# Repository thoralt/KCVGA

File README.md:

# KCVGA
This project aims to convert the video output of old KC85/4 computer systems into a VGA signal for display on a modern monitor. The hosts video signals are sampled from the mainboard into an SRAM using an Xilinx Spartan 3A FPGA. The FPGA also generates the VGA video signal from the sampled image. A PIC32MX250F128B contains the FPGA bitstream and loads it during power-up. Additionally, the PIC32 serves as a USB bridge to the FPGA.

## First Prototype

## Second Prototype

# Schematic

# FPGA

## Clock generation

The input clock of 48 MHz is being fed into a DCM to generate the video clock of 108 MHz. This clock drives the states of all other modules inside the FPGA (_KCVIDEO_INTERFACE_, _PIC32_INTERFACE_, _ROM_, _SRAM_INTERFACE_, _VGA_OUTPUT_ and the FIFOs).

## KCVIDEO_INTERFACE

The module _KCVIDEO_INTERFACE_ FPGA has the purpose to pull the pixel data off the mainboard while the KC85 is generating its video signal. It taps into the color and brightness signals (_R_, _G_, _B_, _EX_, _EZ_) as well as the clock signals (_KC_CLK_, _KC_HSYNC_, _KC_VSYNC_). 

To enhance the fault tolerance, the clock and synchronization signals are fed through glitch filters and edge detectors. A falling edge on _KC_VSYNC_ starts a new frame which resets the current line number and SRAM address. A falling edge on _KC_HSYNC_ resets the column counter. On every rising edge of the pixel clock _KC_CLK_ all five pixel data bits are read into a temporary register and the SRAM address ist incremented. After three pixels have been read, these pixels are combined with the 16 bit SRAM address to form a 31 bit wide data word which is being fed into a FIFO. This FIFO buffers 512 words and serves as a synchronization object between the _KCVIDEO_INTERFACE_ and the _SRAM_INTERFACE_.

## SRAM_INTERFACE

This module checks the FIFOs connected to _KCVIDEO_INTERFACE_ and _VGA_OUTPUT_ while preferring the _VGA_OUTPUT_ FIFO. The _VGA_OUTPUT_ module initiates a data transfer by writing a new address into the _SRAM_INTERFACE_. In return, the _SRAM_INTERFACE_ starts filling the FIFO with the content of one video line. If no VGA data transfer is active, the _SRAM_INTERFACE_ module checks the other FIFO for new pixel data, which is then written into the SRAM.

## VGA_OUTPUT

The _VGA_OUTPUT_ module generates the timing signals to create a valid VGA signal of 1280 by 1024 pixels. This mode was chosen because the pixels are integer divisible by the resolution of the KC85 (320 by 256). At the beginning of each line the module requests pixel data from the _SRAM_INTERFACE_ by writing a new address. The FIFO is then starting to fill and at the end of the horizontal sync pulse the first pixels are available to be written to the outputs. The KC pixel data is being mapped to a fixed color space of 4 bit R, G and B values.

## PIC32_INTERFACE

This module allows the PIC32 microcontroller to access the SRAM. Since the PIC32MX250F128B does not support USB High Speed, we're limited to approximately 1 megabyte per second which is close, but not enough to transport the 1.28 MB/s image stream (5 bits, 320 columns, 256 rows, 25 frames). An experimental video streaming implementation might be available later in the design process.

# PIC32 Firmware

tbd

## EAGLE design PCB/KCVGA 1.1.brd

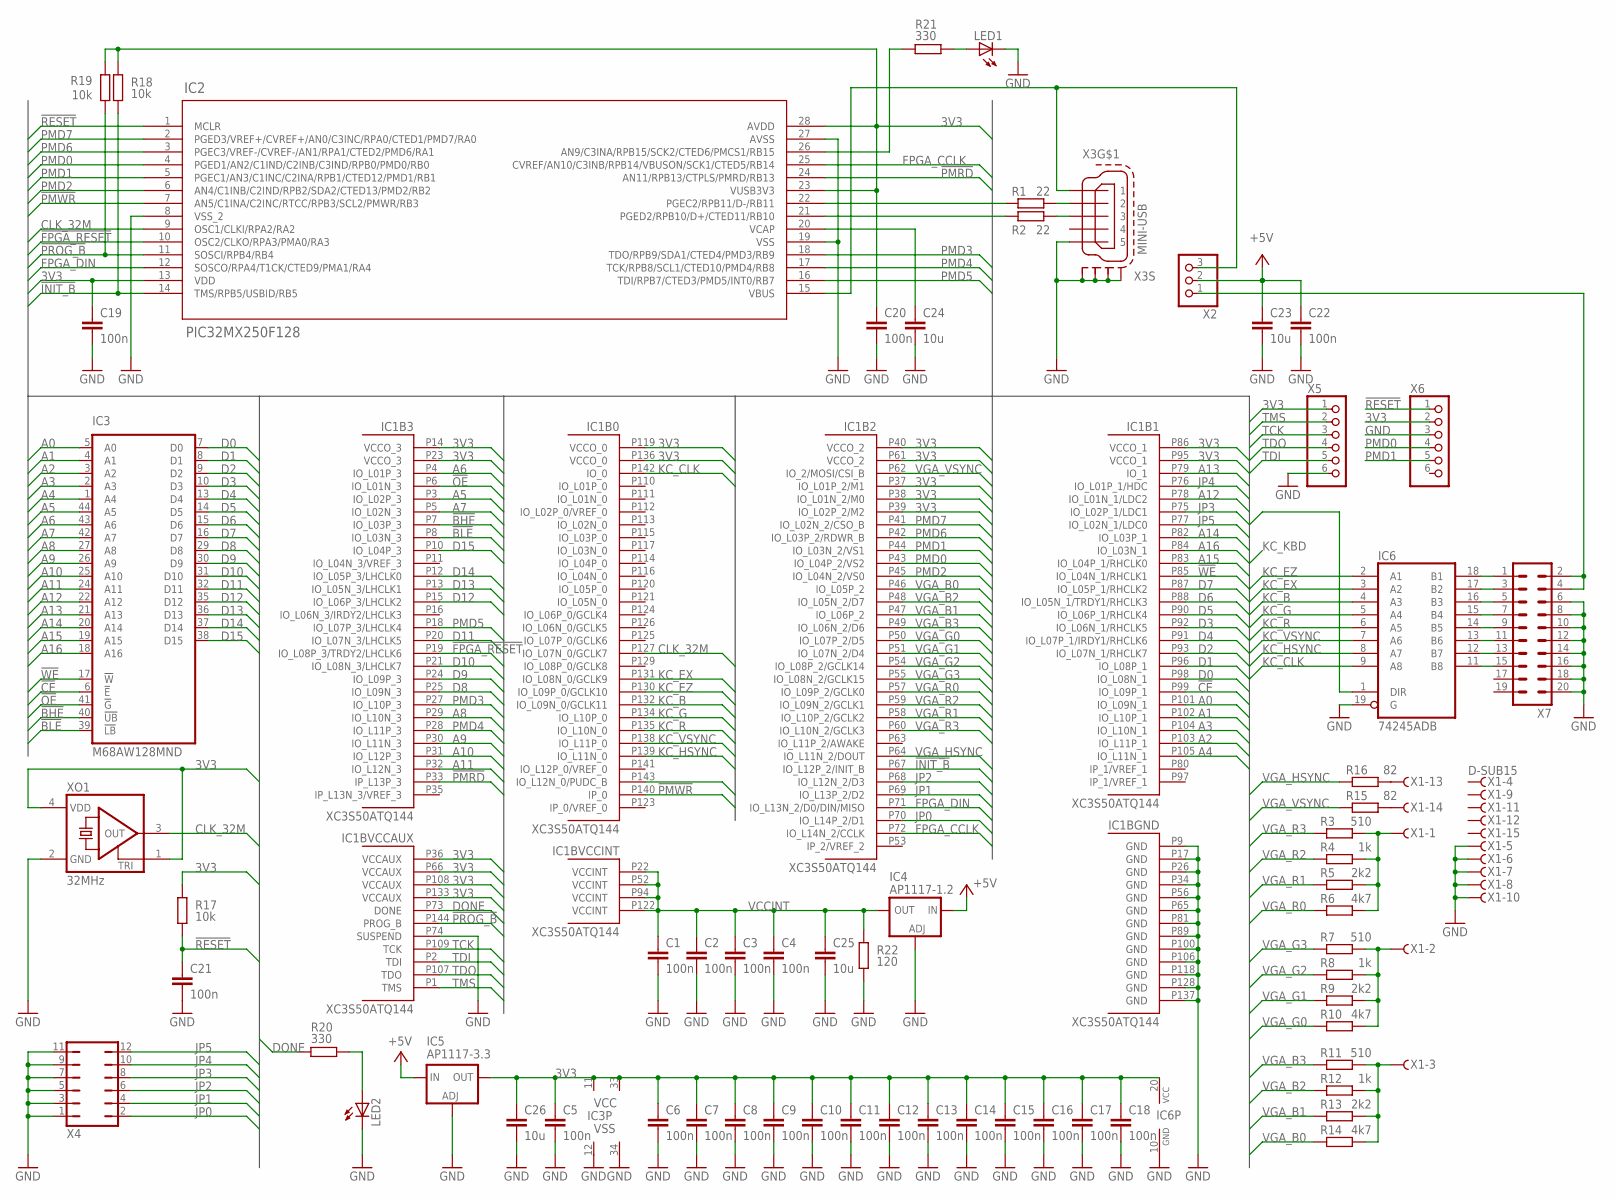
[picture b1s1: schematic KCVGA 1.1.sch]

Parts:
C1, C2, C3, C4, C5, C6, C7, C8, C9, C10, C11, C12, C13, C14, C15, C16, C17, C18, C19, C20, C21, C22: 100n; C0603K
C23, C24, C25, C26: 10u; C1206K
IC1: XC3S50ATQ144; TQ144
IC2: PIC32MX250F128; SSOP28_MC
IC3: M68AW128MND; TSOP44-II
IC4: AP1117-1.2; SOT223
IC5: AP1117-3.3; SOT223
IC6: 74245ADB; SSOP20D8
LED1, LED2: LEDCHIPLED_0603; CHIPLED_0603
R1, R2: 22; R0603
R3, R7, R11: 510; R0603
R4, R8, R12: 1k; R0603
R5, R9, R13: 2k2; R0603
R6, R10, R14: 4k7; R0603
R15, R16: 82; R0603
R17, R18, R19: 10k; R0603
R20, R21: 330; R0603
R22: 120; R0603
X1: D-SUB15; HDR15RA
X2: PINHD-1X3; 1X03
X3: MINI-USB; 32005-301
X4: JP6Q
X5, X6: PINHD-1X6; 1X06
X7: ML20
XO1: 32MHz; ASE

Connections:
3V3: C5.1, C6.1, C7.1, C8.1, C9.1, C10.1, C11.1, C12.1, C13.1, C14.1, C15.1, C16.1, C17.1, C18.1, C19.1, C20.1, C26.1, IC1.P14 (VCCO_3), IC1.P23 (VCCO_3), IC1.P36 (VCCAUX), IC1.P37 (IO_L01P_2/M1), IC1.P38 (IO_L01N_2/M0), IC1.P39 (IO_L02P_2/M2), IC1.P40 (VCCO_2), IC1.P61 (VCCO_2), IC1.P66 (VCCAUX), IC1.P86 (VCCO_1), IC1.P95 (VCCO_1), IC1.P108 (VCCAUX), IC1.P119 (VCCO_0), IC1.P133 (VCCAUX), IC1.P136 (VCCO_0), IC1.P143 (IO_L12N_0/PUDC_B), IC2.13 (VDD), IC2.23 (VUSB3V3), IC2.28 (AVDD), IC3.11 (VCC), IC3.33 (VCC), IC5.4 (OUT), IC6.1 (DIR), IC6.20 (VCC), R17.2, R18.2, R19.2, X5.1, X6.2, XO1.1 (TRI), XO1.4 (VDD)
!BHE: IC1.P7 (IO_L03P_3), IC3.40 (!UB)
!BLE: IC1.P8 (IO_L03N_3), IC3.39 (!LB)
!CE: IC1.P99 (IO_L09P_1), IC3.6 (!E)
!FPGA_RESET: IC1.P19 (IO_L08P_3/TRDY2/LHCLK6), IC2.10 (OSC2/CLKO/RPA3/PMA0/RA3)
!INIT_B: IC1.P67 (IO_L12P_2/INIT_B), IC2.14 (TMS/RPB5/USBID/RB5), R18.1
!OE: IC1.P6 (IO_L01N_3), IC3.41 (!G)
!PMRD: IC1.P33 (IP_L13P_3), IC2.24 (AN11/RPB13/CTPLS/PMRD/RB13)
!PMWR: IC1.P140 (IP_0), IC2.7 (AN5/C1INA/C2INC/RTCC/RPB3/SCL2/PMWR/RB3)
!PROG_B: IC1.P144 (PROG_B), IC2.11 (SOSCI/RPB4/RB4), R19.1
!RESET: C21.1, IC2.1 (MCLR), R17.1, X6.1
!WE: IC1.P85 (IO_L04N_1/RHCLK1), IC3.17 (!W)
+5V: C22.1, C23.1, IC4.3 (IN), IC5.3 (IN), X2.2
A0: IC1.P101 (IO_L09N_1), IC3.5 (A0)
A1: IC1.P102 (IO_L10P_1), IC3.4 (A1)
A2: IC1.P103 (IO_L11P_1), IC3.3 (A2)
A3: IC1.P104 (IO_L10N_1), IC3.2 (A3)
A4: IC1.P105 (IO_L11N_1), IC3.1 (A4)
A5: IC1.P3 (IO_L02P_3), IC3.44 (A5)
A6: IC1.P4 (IO_L01P_3), IC3.43 (A6)
A7: IC1.P5 (IO_L02N_3), IC3.42 (A7)
A8: IC1.P29 (IO_L10N_3), IC3.27 (A8)
A9: IC1.P30 (IO_L11N_3), IC3.26 (A9)
A10: IC1.P31 (IO_L12P_3), IC3.25 (A10)
A11: IC1.P32 (IO_L12N_3), IC3.24 (A11)
A12: IC1.P78 (IO_L01N_1/LDC2), IC3.22 (A12)
A13: IC1.P79 (IO_1), IC3.21 (A13)
A14: IC1.P82 (IO_L03P_1), IC3.20 (A14)
A15: IC1.P83 (IO_L04P_1/RHCLK0), IC3.19 (A15)
A16: IC1.P84 (IO_L03N_1), IC3.18 (A16)
CLK_32M: IC1.P127 (IO_L07N_0/GCLK7), IC2.9 (OSC1/CLKI/RPA2/RA2), XO1.3 (OUT)
D0: IC1.P98 (IO_L08N_1), IC3.7 (D0)
D1: IC1.P96 (IO_L08P_1), IC3.8 (D1)
D2: IC1.P93 (IO_L07N_1/RHCLK7), IC3.9 (D2)
D3: IC1.P92 (IO_L06N_1/RHCLK5), IC3.10 (D3)
D4: IC1.P91 (IO_L07P_1/IRDY1/RHCLK6), IC3.13 (D4)
D5: IC1.P90 (IO_L06P_1/RHCLK4), IC3.14 (D5)
D6: IC1.P88 (IO_L05N_1/TRDY1/RHCLK3), IC3.15 (D6)
D7: IC1.P87 (IO_L05P_1/RHCLK2), IC3.16 (D7)
D8: IC1.P25 (IO_L09N_3), IC3.29 (D8)
D9: IC1.P24 (IO_L09P_3), IC3.30 (D9)
D10: IC1.P21 (IO_L08N_3/LHCLK7), IC3.31 (D10)
D11: IC1.P20 (IO_L07N_3/LHCLK5), IC3.32 (D11)
D12: IC1.P15 (IO_L06P_3/LHCLK2), IC3.35 (D12)
D13: IC1.P13 (IO_L05N_3/LHCLK1), IC3.36 (D13)
D14: IC1.P12 (IO_L05P_3/LHCLK0), IC3.37 (D14)
D15: IC1.P10 (IO_L04P_3), IC3.38 (D15)
DONE: IC1.P73 (DONE), R20.1
FPGA_CCLK: IC1.P72 (IO_L14N_2/CCLK), IC2.25 (CVREF/AN10/C3INB/RPB14/VBUSON/SCK1/CTED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)
FPGA_DIN: IC1.P71 (IO_L13N_2/D0/DIN/MISO), IC2.12 (SOSCO/RPA4/T1CK/CTED9/PMA1/RA4)
GND: C1.2, C2.2, C3.2, C4.2, C5.2, C6.2, C7.2, C8.2, C9.2, C10.2, C11.2, C12.2, C13.2, C14.2, C15.2, C16.2, C17.2, C18.2, C19.2, C20.2, C21.2, C22.2, C23.2, C24.2, C25.2, C26.2, IC1.P9 (GND), IC1.P17 (GND), IC1.P26 (GND), IC1.P34 (GND), IC1.P56 (GND), IC1.P65 (GND), IC1.P74 (SUSPEND), IC1.P81 (GND), IC1.P89 (GND), IC1.P100 (GND), IC1.P106 (GND), IC1.P118 (GND), IC1.P128 (GND), IC1.P137 (GND), IC2.8 (VSS_2), IC2.19 (VSS), IC2.27 (AVSS), IC3.12 (VSS), IC3.34 (VSS), IC4.1 (ADJ), IC5.1 (ADJ), IC6.10 (GND), IC6.19 (G), LED1.C, LED2.C, R22.1, X1.5, X1.6, X1.7, X1.8, X1.10, X3.5, X3.M1 (S1), X3.M2 (S2), X3.M3 (S3), X3.M4 (S4), X4.1, X4.3, X4.5, X4.7, X4.9, X4.11, X5.6, X6.3, X7.6, X7.8, X7.10, X7.12, X7.14, X7.16, X7.18, X7.20, XO1.2 (GND)
JP0: IC1.P70 (IO_L14P_2/D1), X4.2
JP1: IC1.P69 (IO_L13P_2/D2), X4.4
JP2: IC1.P68 (IO_L12N_2/D3), X4.6
JP3: IC1.P75 (IO_L02P_1/LDC1), X4.8
JP4: IC1.P76 (IO_L01P_1/HDC), X4.10
JP5: IC1.P77 (IO_L02N_1/LDC0), X4.12
KC_B: IC1.P132 (IO_L09N_0/GCLK11), IC6.4 (A3)
KC_CLK: IC1.P142 (IO_0), IC6.9 (A8)
KC_EX: IC1.P131 (IO_L08N_0/GCLK9), IC6.3 (A2)
KC_EZ: IC1.P130 (IO_L09P_0/GCLK10), IC6.2 (A1)
KC_G: IC1.P134 (IO_L10P_0), IC6.5 (A4)
KC_HSYNC: IC1.P139 (IO_L11N_0), IC6.8 (A7)
KC_R: IC1.P135 (IO_L10N_0), IC6.6 (A5)
KC_VSYNC: IC1.P138 (IO_L11P_0), IC6.7 (A6)
unnamed: IC2.15 (VBUS), X2.3, X3.1
unnamed: IC6.18 (B1), X7.1
unnamed: IC6.17 (B2), X7.3
unnamed: IC6.16 (B3), X7.5
unnamed: IC6.15 (B4), X7.7
unnamed: IC6.14 (B5), X7.9
unnamed: IC6.13 (B6), X7.11
unnamed: IC6.12 (B7), X7.13
unnamed: IC6.11 (B8), X7.15
unnamed: R16.2, X1.13
unnamed: IC2.22 (PGEC2/RPB11/D-/RB11), R1.1
unnamed: IC2.21 (PGED2/RPB10/D+/CTED11/RB10), R2.1
unnamed: R1.2, X3.2
unnamed: R2.2, X3.3
unnamed: R15.2, X1.14
unnamed: C24.1, IC2.20 (VCAP)
unnamed: R11.2, R12.2, R13.2, R14.2, X1.3
unnamed: R7.2, R8.2, R9.2, R10.2, X1.2
unnamed: R3.2, R4.2, R5.2, R6.2, X1.1
unnamed: X2.1, X7.2, X7.4
unnamed: LED2.A, R20.2
unnamed: IC2.26 (AN9/C3INA/RPB15/SCK2/CTED6/PMCS1/RB15), R21.1
unnamed: LED1.A, R21.2
PMD0: IC1.P43 (IO_L04P_2/VS2), IC2.4 (PGED1/AN2/C1IND/C2INB/C3IND/RPB0/PMD0/R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), X6.4
PMD1: IC1.P44 (IO_L03N_2/VS1), IC2.5 (PGEC1/AN3/C1INC/C2INA/RPB1/CTED12/PMD1/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), X6.5
PMD2: IC1.P45 (IO_L04N_2/VS0), IC2.6 (AN4/C1INB/C2IND/RPB2/SDA2/CTED13/PMD2/R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)
PMD3: IC1.P27 (IO_L10P_3), IC2.18 (TDO/RPB9/SDA1/CTED4/PMD3/RB9)
PMD4: IC1.P28 (IO_L11P_3), IC2.17 (TCK/RPB8/SCL1/CTED10/PMD4/RB8)
PMD5: IC1.P18 (IO_L07P_3/LHCLK4), IC2.16 (TDI/RPB7/CTED3/PMD5/INT0/RB7)
PMD6: IC1.P42 (IO_L03P_2/RDWR_B), IC2.3 (PGEC3/VREF-/CVREF-/AN1/RPA1/CTED2/PMD6/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)
PMD7: IC1.P41 (IO_L02N_2/CSO_B), IC2.2 (PGED3/VREF+/CVREF+/AN0/C3INC/RPA0/CTED1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)
TCK: IC1.P109 (TCK), X5.3
TDI: IC1.P2 (TDI), X5.5
TDO: IC1.P107 (TDO), X5.4
TMS: IC1.P1 (TMS), X5.2
VCCINT: C1.1, C2.1, C3.1, C4.1, C25.1, IC1.P22 (VCCINT), IC1.P52 (VCCINT), IC1.P94 (VCCINT), IC1.P122 (VCCINT), IC4.4 (OUT), R22.2
VGA_B0: IC1.P46 (IO_L05P_2), R14.1
VGA_B1: IC1.P47 (IO_L06P_2), R13.1
VGA_B2: IC1.P48 (IO_L05N_2/D7), R12.1
VGA_B3: IC1.P49 (IO_L06N_2/D6), R11.1
VGA_G0: IC1.P50 (IO_L07P_2/D5), R10.1
VGA_G1: IC1.P51 (IO_L07N_2/D4), R9.1
VGA_G2: IC1.P54 (IO_L08P_2/GCLK14), R8.1
VGA_G3: IC1.P55 (IO_L08N_2/GCLK15), R7.1
VGA_HSYNC: IC1.P64 (IO_L11N_2/DOUT), R16.1
VGA_R0: IC1.P57 (IO_L09P_2/GCLK0), R6.1
VGA_R1: IC1.P58 (IO_L10P_2/GCLK2), R5.1
VGA_R2: IC1.P59 (IO_L09N_2/GCLK1), R4.1
VGA_R3: IC1.P60 (IO_L10N_2/GCLK3), R3.1
VGA_VSYNC: IC1.P62 (IO_2/MOSI/CSI_B), R15.1

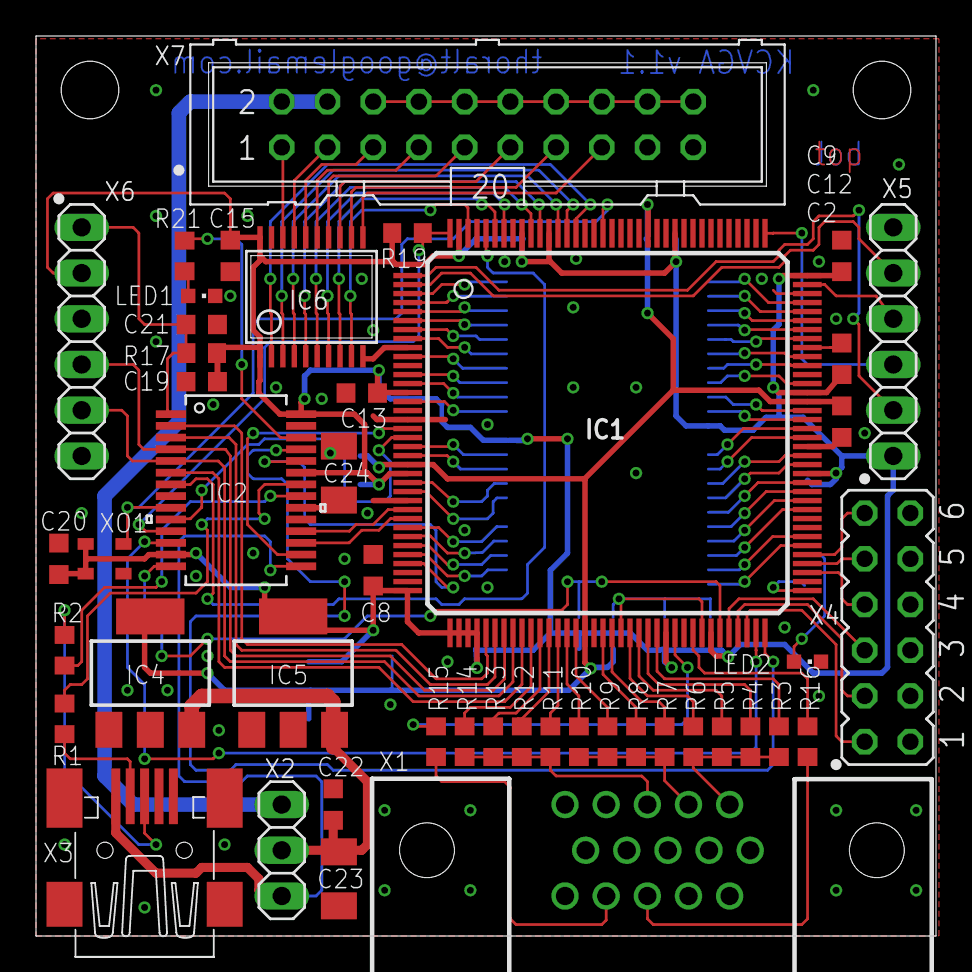
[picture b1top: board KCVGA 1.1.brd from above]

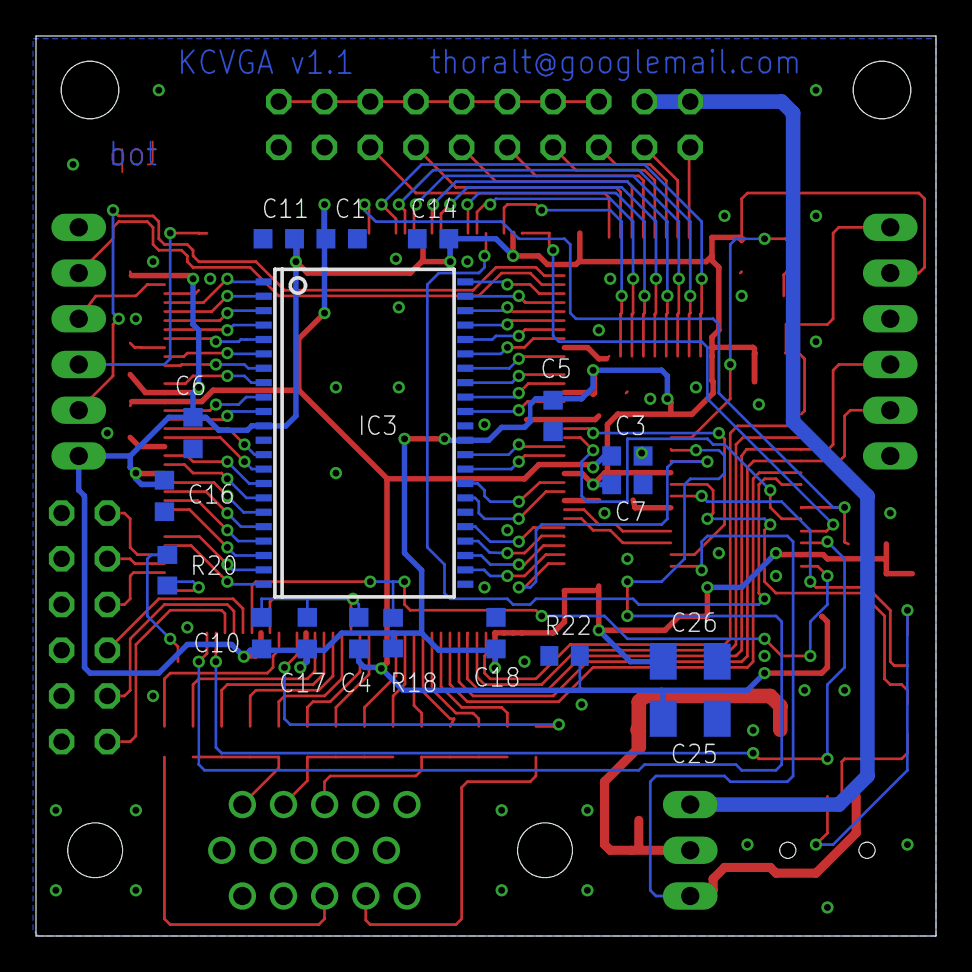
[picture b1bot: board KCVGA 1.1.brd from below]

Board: 2 copper layers, 50.0 x 50.0 mm, 64 parts (18 on the bottom side), 115 nets.

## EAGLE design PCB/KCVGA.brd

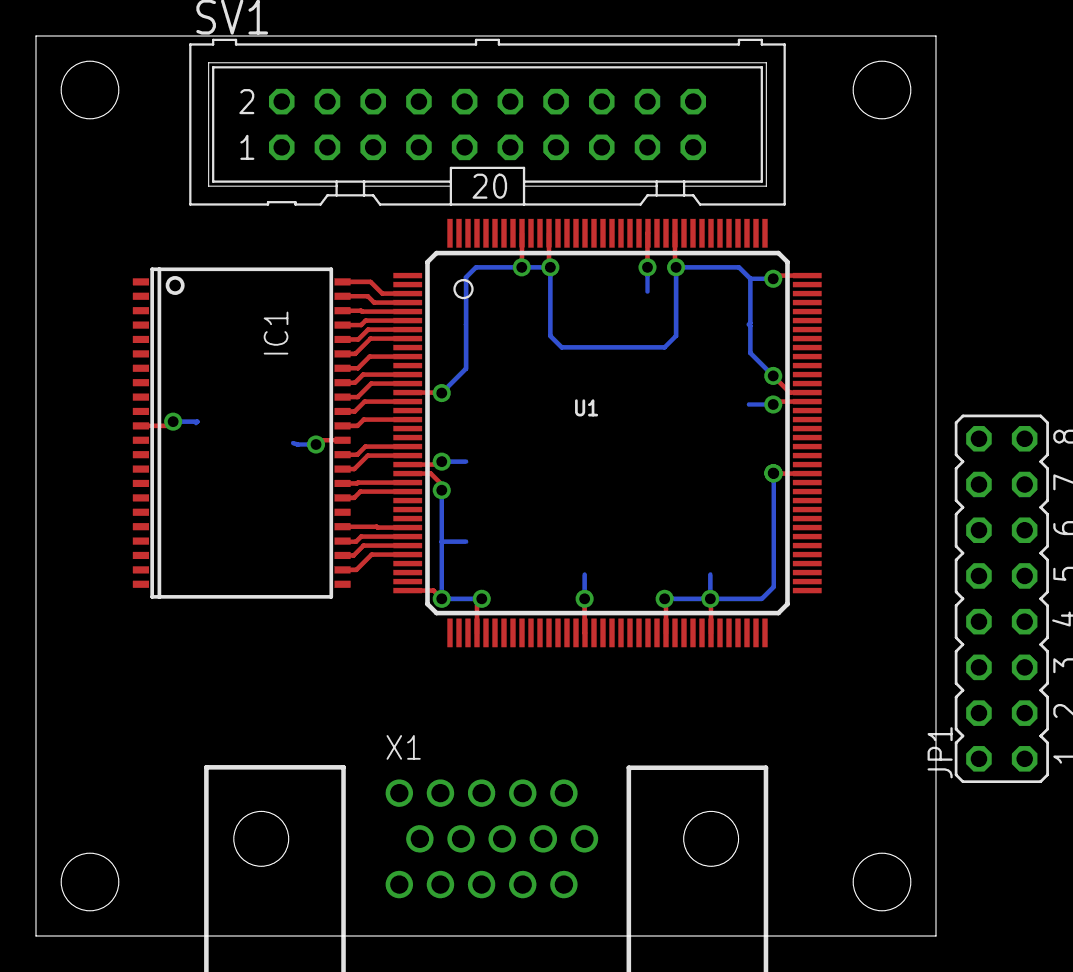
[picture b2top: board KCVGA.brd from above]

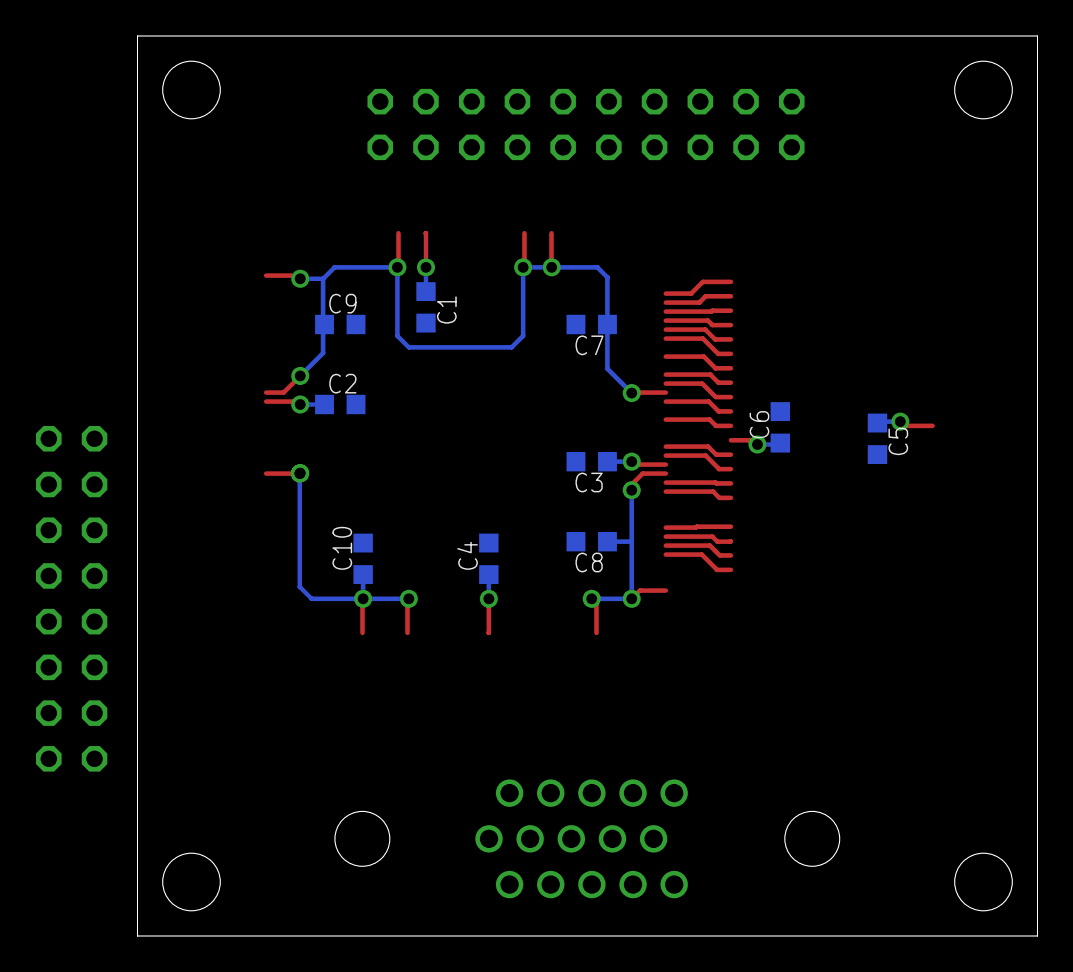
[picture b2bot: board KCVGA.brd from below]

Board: 2 copper layers, 50.0 x 50.0 mm, 15 parts (10 on the bottom side), 22 nets.

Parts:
C1, C2, C3, C4, C5, C6, C7, C8, C9, C10: 100n; C0603K
IC1: M68AW128MND; TSOP44-II
JP1: JP8Q
SV1: ML20
U1: XC3S50ATQ144; TQ144
X1: D-SUB15-HDR15RA; HDR15RA

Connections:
3V3: C5.1, C6.1, C7.1, C8.1, C9.1, C10.1, IC1.11, IC1.33, U1.P14, U1.P23, U1.P36, U1.P40, U1.P61, U1.P66, U1.P86, U1.P95, U1.P108, U1.P119, U1.P133, U1.P136
+5V: SV1.18, SV1.20
A5: IC1.44, U1.P3
A6: IC1.43, U1.P4
A7: IC1.42, U1.P5
A8: IC1.27, U1.P29
A9: IC1.26, U1.P30
A10: IC1.25, U1.P31
A11: IC1.24, U1.P32
BHE: IC1.40, U1.P7
BLE: IC1.39, U1.P8
D8: IC1.29, U1.P25
D9: IC1.30, U1.P24
D10: IC1.31, U1.P21
D11: IC1.32, U1.P20
D12: IC1.35, U1.P15
D13: IC1.36, U1.P13
D14: IC1.37, U1.P12
D15: IC1.38, U1.P10
GND: C1.2, C2.2, C3.2, C4.2, C5.2, C6.2, C7.2, C8.2, C9.2, C10.2, IC1.12, IC1.34, SV1.2, SV1.4, SV1.6, SV1.8, SV1.10, SV1.12, SV1.14, SV1.16, U1.P9, U1.P17, U1.P26, U1.P34, U1.P56, U1.P65, U1.P81, U1.P89, U1.P100, U1.P106, U1.P118, U1.P128, U1.P137
OE: IC1.41, U1.P6
VCCINT: C1.1, C2.1, C3.1, C4.1, U1.P22, U1.P52, U1.P94, U1.P122

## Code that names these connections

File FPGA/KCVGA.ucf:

# external clock 48 MHz
NET "pin_CLK" LOC = p127 | CLOCK_DEDICATED_ROUTE = FALSE | IOSTANDARD = LVCMOS33 | TNM_NET = "TNM_CLK_IN";
TIMESPEC TS_CLK_IN = PERIOD "TNM_CLK_IN" 20.833000 ns HIGH 50 %;

NET "pin_nRESET" LOC = p67 | IOSTANDARD = LVCMOS33 | PULLUP; # shared with INIT_B

#NET "pin_JUMPER0" LOC = p70 | IOSTANDARD = LVCMOS33 | PULLUP; # JP0
#NET "JP1" LOC = p69 | IOSTANDARD = LVCMOS33 | PULLUP;
#NET "JP2" LOC = p68 | IOSTANDARD = LVCMOS33 | PULLUP;
#NET "JP3" LOC = p75 | IOSTANDARD = LVCMOS33 | PULLUP;
#NET "JP4" LOC = p76 | IOSTANDARD = LVCMOS33 | PULLUP;
#NET "JP5" LOC = p77 | IOSTANDARD = LVCMOS33 | PULLUP;

#NET "TEST1" LOC = p115 | IOSTANDARD = LVCMOS33;
#NET "TEST2" LOC = p117 | IOSTANDARD = LVCMOS33;
#NET "TEST3" LOC = P138 | IOSTANDARD = LVCMOS33;
#NET "TEST4" LOC = P29 | IOSTANDARD = LVCMOS33;

#NET "pin_KC_CLK" LOC = p142 | IOSTANDARD = LVCMOS33 | PULLDOWN;
#NET "pin_KC_R" LOC = p135 | IOSTANDARD = LVCMOS33 | PULLDOWN;
#NET "pin_KC_G" LOC = p134 | IOSTANDARD = LVCMOS33 | PULLDOWN;
#NET "pin_KC_B" LOC = p132 | IOSTANDARD = LVCMOS33 | PULLDOWN;
#NET "pin_KC_HSYNC" LOC = p139 | IOSTANDARD = LVCMOS33 | PULLDOWN;
#NET "pin_KC_EZ" LOC = p130 | IOSTANDARD = LVCMOS33 | PULLDOWN;
#NET "pin_KC_EX" LOC = p131 | IOSTANDARD = LVCMOS33 | PULLDOWN;
#NET "pin_KC_VSYNC" LOC = p138 | IOSTANDARD = LVCMOS33 | PULLDOWN;

NET "pin_PIC32_DATA[7]" LOC = p41 | IOSTANDARD = LVCMOS33 | SLEW = FAST | PULLUP;
NET "pin_PIC32_DATA[6]" LOC = p42 | IOSTANDARD = LVCMOS33 | SLEW = FAST | PULLUP;
NET "pin_PIC32_DATA[5]" LOC = p18 | IOSTANDARD = LVCMOS33 | SLEW = FAST | PULLUP;
NET "pin_PIC32_DATA[4]" LOC = p28 | IOSTANDARD = LVCMOS33 | SLEW = FAST | PULLUP;
NET "pin_PIC32_DATA[3]" LOC = p27 | IOSTANDARD = LVCMOS33 | SLEW = FAST | PULLUP;
NET "pin_PIC32_DATA[2]" LOC = p45 | IOSTANDARD = LVCMOS33 | SLEW = FAST | PULLUP;
NET "pin_PIC32_DATA[1]" LOC = p44 | IOSTANDARD = LVCMOS33 | SLEW = FAST | PULLUP;
NET "pin_PIC32_DATA[0]" LOC = p43 | IOSTANDARD = LVCMOS33 | SLEW = FAST | PULLUP;
NET "pin_PIC32_ADDRESS[1]" LOC = p71 | IOSTANDARD = LVCMOS33 | PULLUP; # shared with DIN
NET "pin_PIC32_ADDRESS[0]" LOC = p19 | IOSTANDARD = LVCMOS33 | PULLUP;
NET "pin_PIC32_nRD" LOC = p33 | IOSTANDARD = LVCMOS33 | SLEW = FAST | PULLUP;
NET "pin_PIC32_nWR" LOC = p140 | IOSTANDARD = LVCMOS33 | SLEW = FAST | PULLUP;

# M68AW128MND 128k x 16 bit
#NET "pin_SRAM_A[16]" LOC = p84;  # SRAM pin 18
#NET "pin_SRAM_A[15]" LOC = p83;  # SRAM pin 19
#NET "pin_SRAM_A[14]" LOC = p82;  # SRAM pin 20
#NET "pin_SRAM_A[13]" LOC = p79;  # SRAM pin 21
#NET "pin_SRAM_A[12]" LOC = p78;  # SRAM pin 22
#NET "pin_SRAM_A[11]" LOC = p32;  # SRAM pin 24
#NET "pin_SRAM_A[10]" LOC = p31;  # SRAM pin 25
#NET "pin_SRAM_A[9]" LOC = p30;   # SRAM pin 26
#NET "pin_SRAM_A[8]" LOC = p29;   # SRAM pin 27
#NET "pin_SRAM_A[7]" LOC = p5;    # SRAM pin 42
#NET "pin_SRAM_A[6]" LOC = p4;    # SRAM pin 43
#NET "pin_SRAM_A[5]" LOC = p3;    # SRAM pin 44
#NET "pin_SRAM_A[4]" LOC = p105;  # SRAM pin 1
#NET "pin_SRAM_A[3]" LOC = p104;  # SRAM pin 2
#NET "pin_SRAM_A[2]" LOC = p103;  # SRAM pin 3
#NET "pin_SRAM_A[1]" LOC = p102;  # SRAM pin 4
#NET "pin_SRAM_A[0]" LOC = p101;  # SRAM pin 5

# CY7C1021DV33 - 64k x 16 bit
# Attention: A12...A15 are shifted by one pin compared to M68AW128MND
NET "pin_SRAM_A[16]" LOC = p78 | IOSTANDARD = LVCMOS33 | SLEW = FAST;           # unused, mapped to SRAM pin 22 (nc)
NET "pin_SRAM_A[15]" LOC = p84 | IOSTANDARD = LVCMOS33 | SLEW = FAST;           # SRAM pin 18
NET "pin_SRAM_A[14]" LOC = p83 | IOSTANDARD = LVCMOS33 | SLEW = FAST;           # SRAM pin 19
NET "pin_SRAM_A[13]" LOC = p82 | IOSTANDARD = LVCMOS33 | SLEW = FAST;           # SRAM pin 20
NET "pin_SRAM_A[12]" LOC = p79 | IOSTANDARD = LVCMOS33 | SLEW = FAST;           # SRAM pin 21
NET "pin_SRAM_A[11]" LOC = p32 | IOSTANDARD = LVCMOS33 | SLEW = FAST;           # SRAM pin 24
NET "pin_SRAM_A[10]" LOC = p31 | IOSTANDARD = LVCMOS33 | SLEW = FAST;           # SRAM pin 25
NET "pin_SRAM_A[9]" LOC = p30 | IOSTANDARD = LVCMOS33 | SLEW = FAST;            # SRAM pin 26
NET "pin_SRAM_A[8]" LOC = p29 | IOSTANDARD = LVCMOS33 | SLEW = FAST;            # SRAM pin 27
NET "pin_SRAM_A[7]" LOC = p5 | IOSTANDARD = LVCMOS33 | SLEW = FAST;             # SRAM pin 42
NET "pin_SRAM_A[6]" LOC = p4 | IOSTANDARD = LVCMOS33 | SLEW = FAST;             # SRAM pin 43
NET "pin_SRAM_A[5]" LOC = p3 | IOSTANDARD = LVCMOS33 | SLEW = FAST;             # SRAM pin 44
NET "pin_SRAM_A[4]" LOC = p105 | IOSTANDARD = LVCMOS33 | SLEW = FAST;           # SRAM pin 1
NET "pin_SRAM_A[3]" LOC = p104 | IOSTANDARD = LVCMOS33 | SLEW = FAST;           # SRAM pin 2
NET "pin_SRAM_A[2]" LOC = p103 | IOSTANDARD = LVCMOS33 | SLEW = FAST;           # SRAM pin 3
NET "pin_SRAM_A[1]" LOC = p102 | IOSTANDARD = LVCMOS33 | SLEW = FAST;           # SRAM pin 4
NET "pin_SRAM_A[0]" LOC = p101 | IOSTANDARD = LVCMOS33 | SLEW = FAST;           # SRAM pin 5
NET "pin_SRAM_D[15]" LOC = p10 | IOSTANDARD = LVCMOS33 | SLEW = FAST;  # SRAM pin 38
NET "pin_SRAM_D[14]" LOC = p12 | IOSTANDARD = LVCMOS33 | SLEW = FAST;  # SRAM pin 37
NET "pin_SRAM_D[13]" LOC = p13 | IOSTANDARD = LVCMOS33 | SLEW = FAST;  # SRAM pin 36
NET "pin_SRAM_D[12]" LOC = p15 | IOSTANDARD = LVCMOS33 | SLEW = FAST;  # SRAM pin 35
NET "pin_SRAM_D[11]" LOC = p20 | IOSTANDARD = LVCMOS33 | SLEW = FAST;  # SRAM pin 32
NET "pin_SRAM_D[10]" LOC = p21 | IOSTANDARD = LVCMOS33 | SLEW = FAST;  # SRAM pin 31
NET "pin_SRAM_D[9]" LOC = p24 | IOSTANDARD = LVCMOS33 | SLEW = FAST;   # SRAM pin 30
NET "pin_SRAM_D[8]" LOC = p25 | IOSTANDARD = LVCMOS33 | SLEW = FAST;   # SRAM pin 29
NET "pin_SRAM_D[7]" LOC = p87 | IOSTANDARD = LVCMOS33 | SLEW = FAST;   # SRAM pin 16
NET "pin_SRAM_D[6]" LOC = p88 | IOSTANDARD = LVCMOS33 | SLEW = FAST;   # SRAM pin 15
NET "pin_SRAM_D[5]" LOC = p90 | IOSTANDARD = LVCMOS33 | SLEW = FAST;   # SRAM pin 14
NET "pin_SRAM_D[4]" LOC = p91 | IOSTANDARD = LVCMOS33 | SLEW = FAST;   # SRAM pin 13
NET "pin_SRAM_D[3]" LOC = p92 | IOSTANDARD = LVCMOS33 | SLEW = FAST;   # SRAM pin 10
NET "pin_SRAM_D[2]" LOC = p93 | IOSTANDARD = LVCMOS33 | SLEW = FAST;   # SRAM pin 9
NET "pin_SRAM_D[1]" LOC = p96 | IOSTANDARD = LVCMOS33 | SLEW = FAST;   # SRAM pin 8
NET "pin_SRAM_D[0]" LOC = p98 | IOSTANDARD = LVCMOS33 | SLEW = FAST;   # SRAM pin 7
NET "pin_SRAM_nBHE" LOC = p7 | IOSTANDARD = LVCMOS33 | SLEW = FAST;    # SRAM pin 40
NET "pin_SRAM_nBLE" LOC = p8 | IOSTANDARD = LVCMOS33 | SLEW = FAST;    # SRAM pin 39
NET "pin_SRAM_nCE" LOC = p99 | IOSTANDARD = LVCMOS33 | SLEW = FAST;    # SRAM pin 6
NET "pin_SRAM_nOE" LOC = p6 | IOSTANDARD = LVCMOS33 | SLEW = FAST;              # SRAM pin 41
NET "pin_SRAM_nWE" LOC = p85 | IOSTANDARD = LVCMOS33 | SLEW = FAST;             # SRAM pin 17

#NET "pin_VGA_B[3]" LOC = p49 | IOSTANDARD = LVCMOS33 | SLEW = FAST;
#NET "pin_VGA_B[2]" LOC = p48 | IOSTANDARD = LVCMOS33 | SLEW = FAST;
#NET "pin_VGA_B[1]" LOC = p47 | IOSTANDARD = LVCMOS33 | SLEW = FAST;
#NET "pin_VGA_B[0]" LOC = p46 | IOSTANDARD = LVCMOS33 | SLEW = FAST;
#NET "pin_VGA_G[3]" LOC = p55 | IOSTANDARD = LVCMOS33 | SLEW = FAST;
#NET "pin_VGA_G[2]" LOC = p54 | IOSTANDARD = LVCMOS33 | SLEW = FAST;
#NET "pin_VGA_G[1]" LOC = p51 | IOSTANDARD = LVCMOS33 | SLEW = FAST;
#NET "pin_VGA_G[0]" LOC = p50 | IOSTANDARD = LVCMOS33 | SLEW = FAST;
#NET "pin_VGA_R[3]" LOC = p60 | IOSTANDARD = LVCMOS33 | SLEW = FAST;
#NET "pin_VGA_R[2]" LOC = p59 | IOSTANDARD = LVCMOS33 | SLEW = FAST;
#NET "pin_VGA_R[1]" LOC = p58 | IOSTANDARD = LVCMOS33 | SLEW = FAST;
#NET "pin_VGA_R[0]" LOC = p57 | IOSTANDARD = LVCMOS33 | SLEW = FAST;
#NET "pin_VGA_HSYNC" LOC = p64 | IOSTANDARD = LVCMOS33 | SLEW = FAST;
#NET "pin_VGA_VSYNC" LOC = p62 | IOSTANDARD = LVCMOS33 | SLEW = FAST;

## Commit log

2015-04-03 PCB: Initial commit
2015-04-03 Added PNG2COE/README.md
2015-04-03 Added crystal oscillator, voltage regulators, FPGA config lines
2015-04-04 completed FPGA configuration interface, tidied up
2015-04-04 added DriveDone to startup options
2015-04-04 PCB: First implementation complete
2015-04-05 Test with PIC32MX270 in TQFP44
2015-04-06 added LDO output caps added Eagle3d files
2015-04-07 Finished silk screen
2015-04-08 optimized silkscreen
2015-04-09 PCB v1.1 production release
2015-04-20 Update README.md
    Added image
2016-02-02 Documentation update
2020-03-11 Added PIC32 firmware
2020-03-11 cleanup
2020-03-12 Code cleanup, refactorization
2020-03-13 added doc, FPGA top level schematic
2020-03-13 added schematic as PNG file
2020-03-17 moved to PIC32 Harmony v3 framework, got USB CDC to work again, FPGA configure now using CDC
2020-03-17 moved to PIC32 Harmony v3 framework
2020-03-17 project cleanup
2020-03-18 Added prototype photos
2020-03-18 code cleanup
2020-03-19 added thumbnails
2020-03-20 fixed SRAM addressing bug, aimplemented PIC32/FPGA interface
2020-03-23 Moved KCVGA-update.py to ncurses, implemented speed benchmark
2021-02-11 Restructured project from Xilinx ISE to Makefile
2021-02-11 Added FPGA/build to .gitignore
2021-02-11 Added bootloader, incomplete
2021-02-11 Changes to work with new FPGA image
2021-02-11 Prepared documentation for timing charts
2021-02-11 Added PIC32/firmware/KCVGA.X/.generated_files
2021-02-11 Added python programmer script for future bootloader
2021-02-12 Switched to VSCode Remote Devcontainer
2021-02-12 Formatting
2021-02-12 Re-added logo
2021-02-12 PIC32 config changes
2021-02-12 Added Xilinx.lic to Dockerfile
2021-02-15 changed color escape sequences
2021-02-15 integration into VSCode build process with error/warning parser
2021-02-15 Added exception handling when input file is gone
2021-02-15 Added BUFG for CLK_108MHZ
2021-02-15 Renamed signals
2021-02-15 stabilized PIC32 interface, added registers for input signals, decoupled processes
2021-02-15 deleted generate.sh (now using Makefile)
2021-02-15 SRAM_Controller now stable, minimal Project compiles without warnings
2021-02-15 changed Makefile paragraph headings from yellow to white
2021-02-15 Added RAM test with random values, bank switching
2021-02-15 Re-enabled and tested PMP functions for FPGA access
2021-02-15 Added A16 to flags register
2021-02-15 improved problemMatcher
2021-02-15 problemMatcher fine tuning
2021-02-15 renamed flag register bit 7 to A16
2021-02-15 separated next state logic from sequential circuit
2021-02-15 Refactored DCM instantiation into module CLK
